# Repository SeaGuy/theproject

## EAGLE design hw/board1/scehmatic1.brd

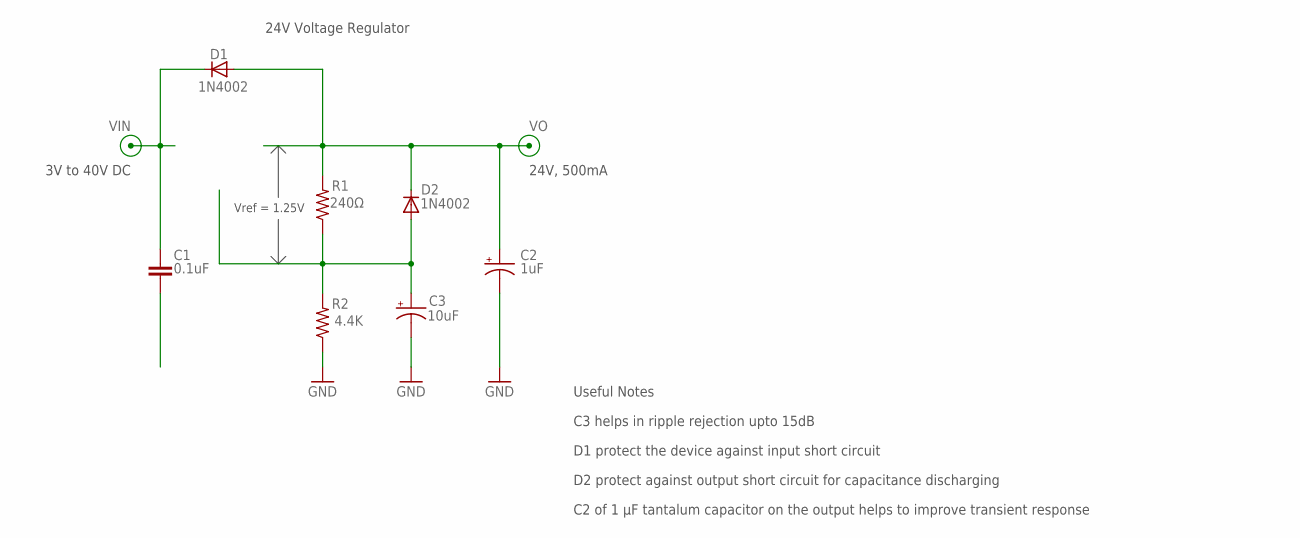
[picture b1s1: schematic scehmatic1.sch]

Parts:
C1: 0.1uF; C075-052X106
C2: 1uF; 085CS_1AR
C3: 10uF; 085CS_1AR
D1, D2: 1N4002; DO41-10
R1: 240Ω; M0805
R2: 4.4K; M0805

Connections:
GND: C2.-, C3.-, R2.1
unnamed: C3.+, D2.A, R1.1, R2.2
VIN: C1.1, D1.C
VO: C2.+, D1.A, D2.C, R1.2

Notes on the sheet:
24V Voltage Regulator
C3 helps in ripple rejection upto 15dB
D1 protect the device against input short circuit
D2 protect against output short circuit for capacitance discharging
C2 of 1 µF tantalum capacitor on the output helps to improve transient response
Useful Notes
24V, 500mA
Vref = 1.25V
3V to 40V DC

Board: 2 copper layers, 7 parts (0 on the bottom side), 4 nets, no tracks yet.

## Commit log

2017-02-22 added RXTX as maven dependency
2017-02-22 update POM with jre dependency
2017-02-23 add jre dependency in POM
2018-06-14 added xdot sim file
2018-06-14 added nodered Eclipse project to local repo
2018-06-18 added docx, pdf and visio to architecture folder
2018-06-18 modified Word document
2018-06-19 added directory for requirements and a requirements document in it
2018-06-19 added hw directory and board1 schematic
2018-06-19 added brd file for board 1
2018-06-19 changes to reqs doc
2018-07-05 added a Visio document to investigate diffs
2018-07-06 updated Word doc
2018-07-06 added Eagle schematic file
2018-07-06 added brd file
2018-07-06 deleted component from schematic and thus board
2018-07-10 new directory and file
2018-07-10 added William
2018-07-10 added Bill
2018-07-10 added Guillermo
2018-07-10 added Guillame
2018-07-10 added WillamTheConquerer
2018-07-10 added SimonTheTerrible
2018-07-10 added Catherine
2018-07-10 added Peter
2018-07-11 added Boscito
2018-07-11 added Mighty Bear
2023-08-30 unknown
